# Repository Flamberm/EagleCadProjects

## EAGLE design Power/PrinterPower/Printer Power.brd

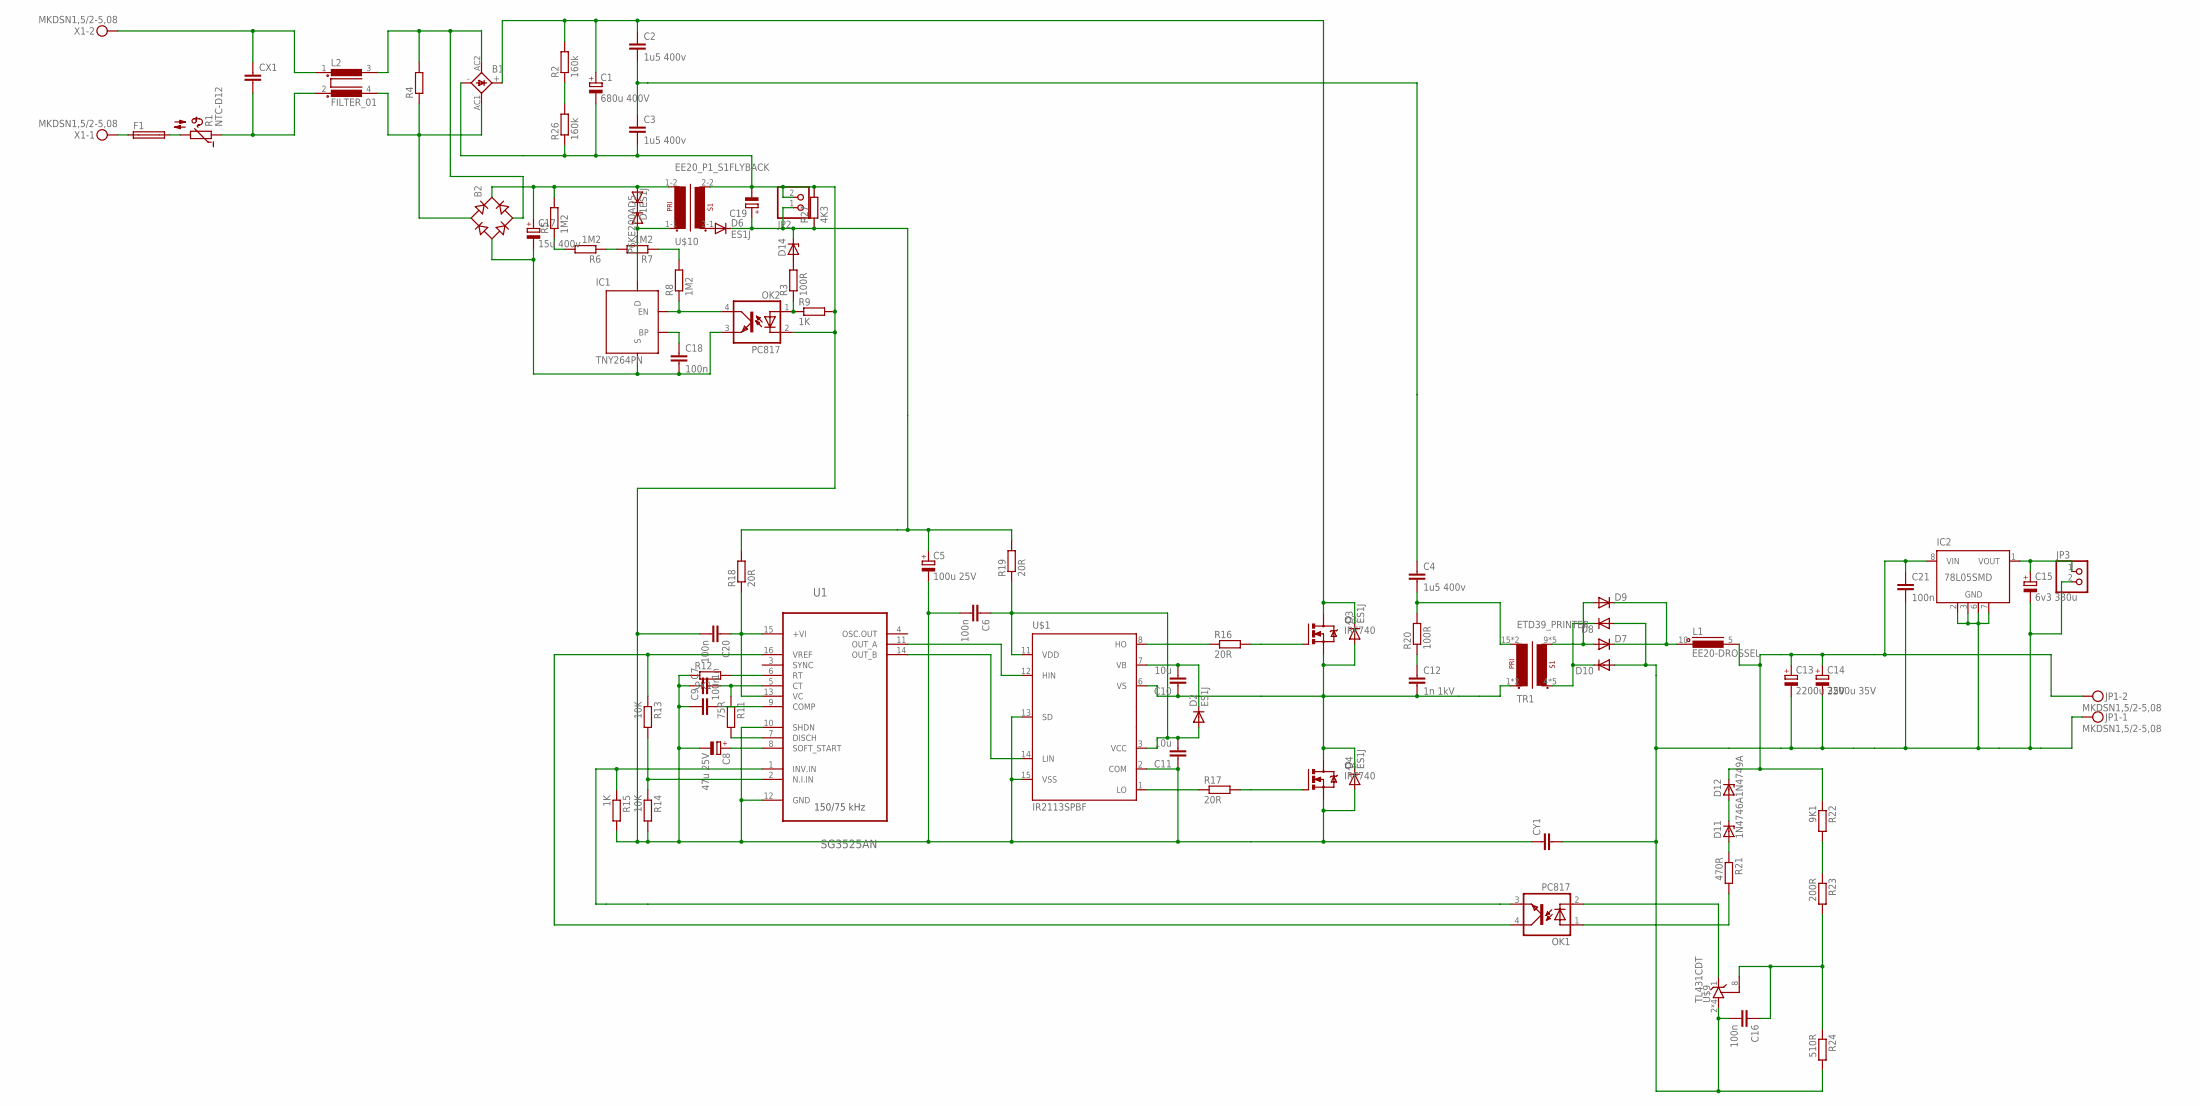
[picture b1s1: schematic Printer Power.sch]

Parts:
B1: KBL
B2: RB1A
C1: 680u 400V; EB35D
C2, C3, C4: 1u5 400v; C225-074X268
C5: 100u 25V; E2,5-7
C6, C9, C16, C18, C20, C21: 100n; C0805
C7: 1n; C0805
C8: 47u 25V; E2,5-7
C10, C11: 10u; C0805
C12: 1n 1kV; C050-025X075
C13, C14: 2200u 35V; E7,5-18
C15: 6v3 330u; E2,5-7
C17: 15u 400v; E5-13
C19: CPOL-EUE2.5-7; E2,5-7
CX1: CXXC15B8; XC15B8
CY1: CYYC10B4; YC10B4
D1: P6KE200A; DO204-10
D2, D3, D4, D5, D6: ES1J; DO214AC
D7, D8, D9, D10: DIODE-DO220S; DO220S
D11: 1N4746A; DO41Z10
D12: 1N4749A; DO41Z10
D14: ZENER-DIODEDO41Z10; DO41Z10
F1: SH22,5
IC1: TNY264PN; DIP-8B
IC2: 78L05SMD; SO08
JP1: MKDSN1,5/2-5,08
JP2, JP3: PINHD-1X2; 1X02
L1: EE20-DROSSEL; EE20_DROSSEL
L2: FILTER_01; 82721K
OK1, OK2: PC817; DIL04
Q3, Q4: IRF740; TO220BV
R1: NTC-D12
R2, R26: 160k; 0207/10
R3: 100R; R0805
R4: R-EU_0309/10; 0309/10
R5, R6, R7, R8: 1M2; R0805
R9, R15: 1K; R0805
R11: 75R; R0805
R12, R22: 9K1; R0805
R13, R14: 10K; R0805
R16, R17: 20R; 0309/12
R18, R19: 20R; R2512
R20: 100R; 0617/17
R21: 470R; R0805
R23: 200R; R0805
R24: 510R; R0805
R27: 4K3; R0805
TR1: ETD39_PRINTER; ETD39_16PIN
U1: SG3525AN; DIP254P762X510-16
U$1: IR2113SPBF; SO16W
U$9: TL431CDT; SO8
U$10: EE20_P1_S1FLYBACK; EE20_P1_S1-REV-4PIN
X1: MKDSN1,5/2-5,08

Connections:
HV-0: B1.-, C1.-, C3.2, C5.-, C6.2, C7.1, C8.-, C9.1, C11.1, C19.-, C20.2, CY1.1, D4.A, JP2.2, OK2.2 (C), Q4.S, R9.2, R12.1, R14.2, R15.2, R26.1, R27.2, U1.10 (SHDN), U1.12 (GND), U$1.2 (COM), U$1.13 (SD), U$1.15 (VSS), U$10.2-2 (S1-2)
HV-150: C2.2, C3.1, C4.1
HV-300: B1.+, C1.+, C2.1, D3.C, Q3.D, R2.2
unnamed: F1.1, X1.1
unnamed: F1.2, R1.2
unnamed: CX1.2, L2.2 (3), R1.1
unnamed: D7.C, D9.C, L1.10 (1)
unnamed: R16.1, U$1.8 (HO)
unnamed: R17.1, U$1.1 (LO)
unnamed: Q3.G, R16.2
unnamed: OK1.3 (EMIT), R15.1, U1.1 (INV.IN)
unnamed: C4.2, R20.2, TR1.15 (P1-2), TR1.16 (P1-2)
unnamed: C20.1, R18.1, U1.13 (VC), U1.15 (+VI)
unnamed: B1.AC1 (AC2), B2.AC1, L2.4, R4.1
unnamed: CX1.1, L2.1, X1.2
unnamed: B2.-, C17.-, C18.2, IC1.2 (S), IC1.3 (S), IC1.7 (S), IC1.8 (S), OK2.3 (EMIT)
unnamed: B1.AC2 (AC1), B2.AC2, L2.3 (2), R4.2
unnamed: C7.2, R11.1, U1.5 (CT)
unnamed: R11.2, U1.7 (DISCH)
unnamed: Q4.G, R17.2
unnamed: U1.11 (OUT_A), U$1.12 (HIN)
unnamed: U1.14 (OUT_B), U$1.14 (LIN)
unnamed: R12.2, U1.6 (RT)
unnamed: C8.+, U1.8 (SOFT_START)
unnamed: C9.2, U1.9 (COMP)
unnamed: OK1.4 (COL), R13.1, U1.16 (VREF)
unnamed: R13.2, R14.1, U1.2 (N.I.IN)
unnamed: IC1.4 (EN), OK2.4 (COL), R8.1
unnamed: C13.-, C14.-, C15.-, C16.2, C21.2, CY1.2, D8.A, D10.A, IC2.2 (GND), IC2.3 (GND), IC2.6 (GND), IC2.7 (GND), JP1.1, JP3.2, R24.2, U$9.2 (A), U$9.3 (A), U$9.6 (A), U$9.7 (A)
unnamed: D8.C, D10.C, TR1.4 (S1-1), TR1.5 (S1-1), TR1.6 (S1-1), TR1.7 (S1-1), TR1.8 (S1-1)
unnamed: R5.1, R6.2
unnamed: R6.1, R7.2
unnamed: C12.1, R20.1
unnamed: D7.A, D9.A, TR1.9 (S1-2), TR1.10 (S1-2), TR1.11 (S1-2), TR1.12 (S1-2), TR1.13 (S1-2)
unnamed: C15.+, IC2.1 (VOUT), JP3.1
unnamed: C13.+, C14.+, C21.1, D12.C, IC2.8 (VIN), JP1.2, L1.5 (2), R22.1
unnamed: D11.C, D12.A
unnamed: D11.A, R21.1
unnamed: OK1.1 (A), R21.2
unnamed: OK1.2 (C), U$9.1 (C)
unnamed: C16.1, R23.2, R24.1, U$9.8 (R)
unnamed: R22.2, R23.1
unnamed: R2.1, R26.2
unnamed: C5.+, C19.+, D6.C, D14.C, JP2.1, R18.2, R19.2, R27.1
unnamed: R7.1, R8.2
unnamed: D1.C, D5.C
unnamed: D5.A, IC1.5 (D), U$10.1-1
unnamed: D14.A, R3.2
unnamed: C18.1, IC1.1 (BP)
unnamed: B2.+, C17.+, D1.A, R5.2, U$10.1-2
unnamed: D6.A, U$10.2-1 (S1-1)
unnamed: OK2.1 (A), R3.1, R9.1
VB: C10.2, D2.C, U$1.7 (VB)
VCC: C6.1, C11.2, D2.A, R19.1, U$1.3 (VCC), U$1.11 (VDD)
VS: C10.1, C12.2, D3.A, D4.C, Q3.S, Q4.D, TR1.1 (P1-1), TR1.2 (P1-1), U$1.6 (VS)

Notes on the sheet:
150/75 kHz

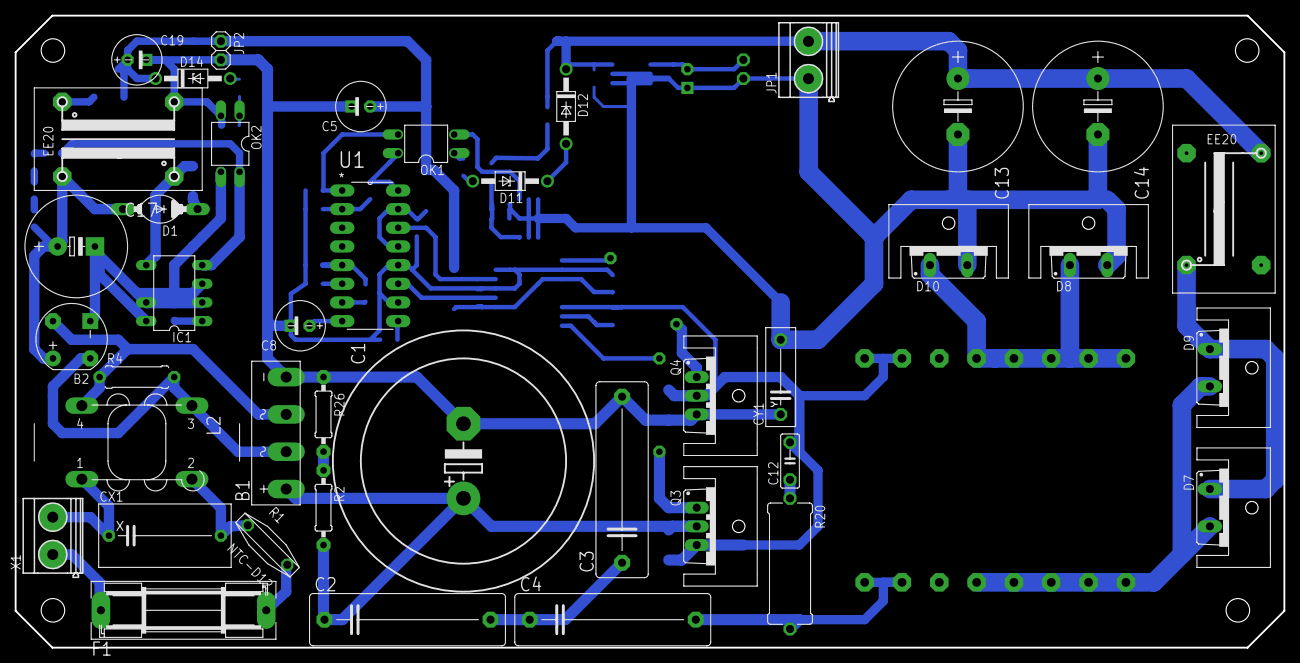
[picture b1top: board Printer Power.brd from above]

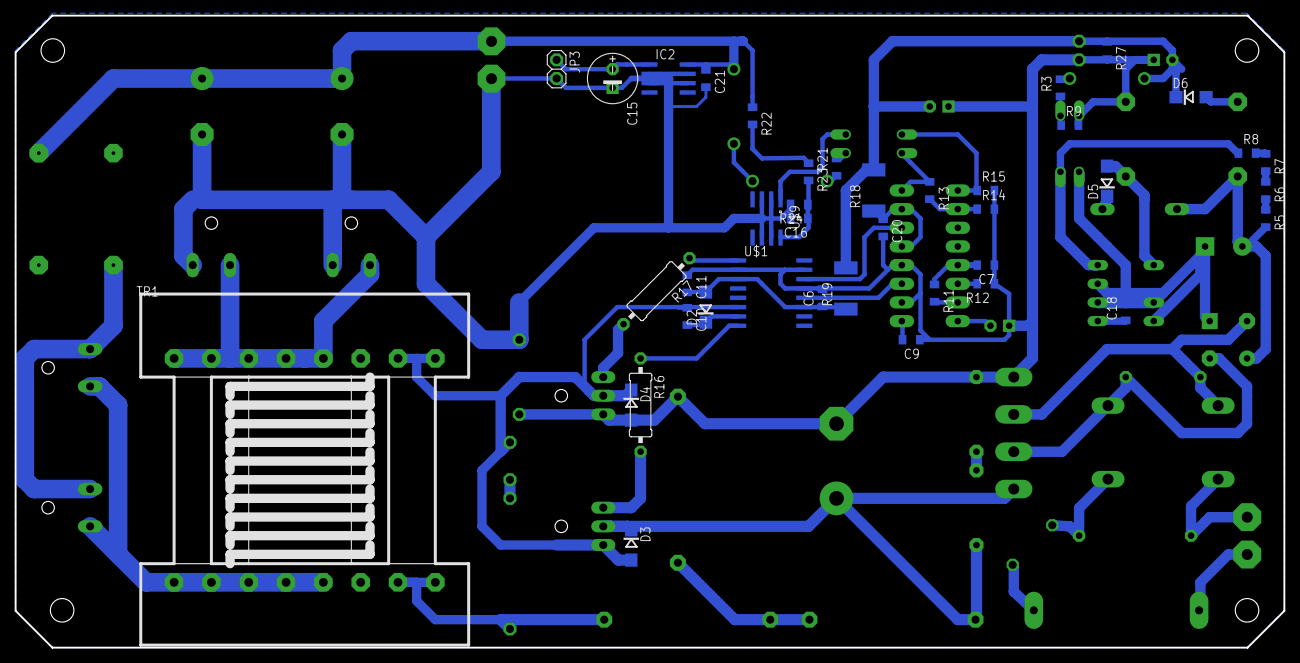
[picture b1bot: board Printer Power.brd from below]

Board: 2 copper layers, 172.7 x 86.0 mm, 87 parts (40 on the bottom side), 55 nets.

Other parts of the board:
U$3, U$4, U$5, U$6, U$7, U$8: SK95-3M3_HOLE

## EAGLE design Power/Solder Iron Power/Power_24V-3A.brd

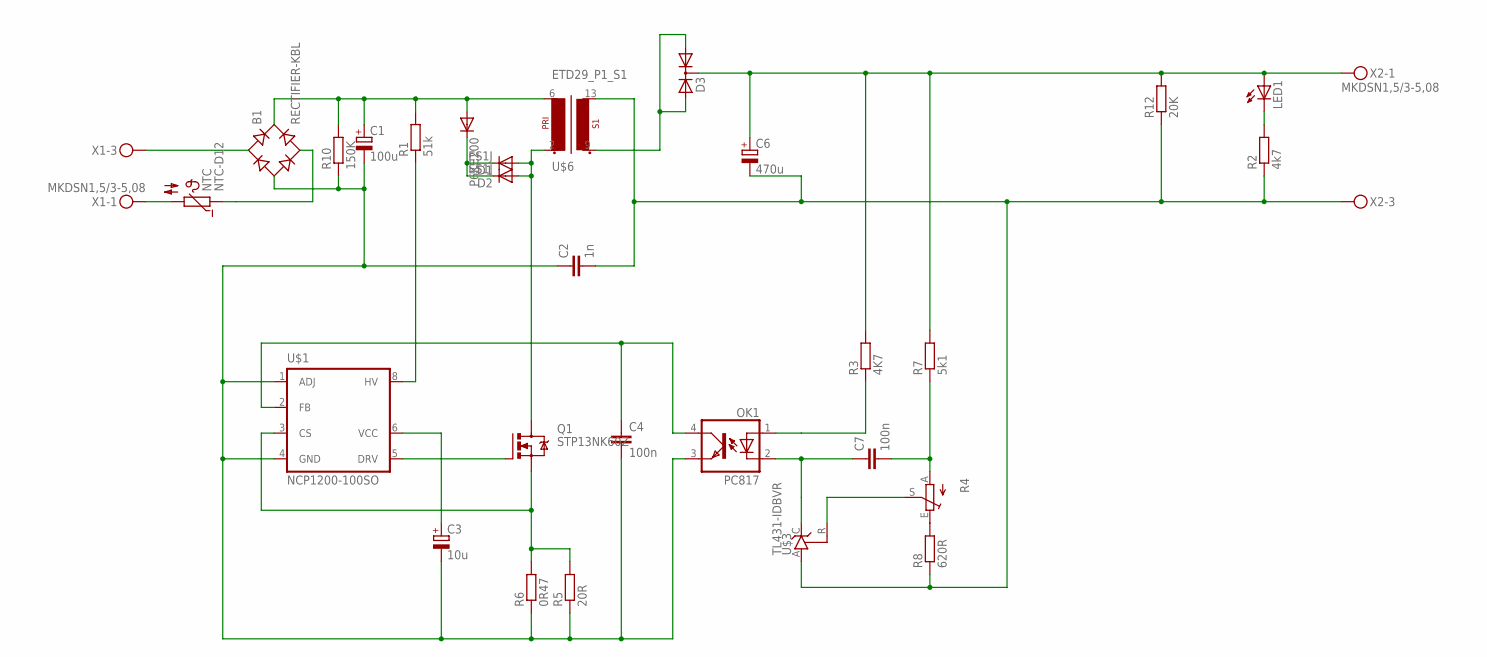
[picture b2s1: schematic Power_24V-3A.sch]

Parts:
B1: RECTIFIER-KBL; KBL
C1: 100u; EB22,5D
C2: 1n; C050-024X044
C3: 10u; E5-5
C4, C7: 100n; C0805
C6: 470u; E5-10,5
D1, D2: ES1J; DO41-7.6
D3: DIODE-2AC|CATO220V; TO220ABS
LED1: LED5MM
NTC: NTC-D12
OK1: PC817; DIL04
P6KE200: DIODE-DO15-12; DO15-12
Q1: STP13NK60Z; TO220BV
R1: 51k; SQP-5
R2: 4k7; R1206
R3: 4K7; R1206
R4: TRIM_EU-S75H; S75H
R5: 20R; 0411/12
R6: 0R47; 0411/12
R7: 5k1; R1206
R8: 620R; R1206
R10: 150K; 0207/10
R12: 20K; R1206
U$1: NCP1200-100SO; SOP8
U$3: TL431-IDBVR; SOT23-5
U$6: ETD29_P1_S1; ETD29
X1, X2: MKDSN1,5/3-5,08

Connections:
unnamed: NTC.2, X1.1
unnamed: B1.AC1, X1.3
unnamed: B1.AC2, NTC.1
unnamed: Q1.S, R5.2, R6.2, U$1.3 (CS)
unnamed: B1.-, C1.-, C2.1, C3.-, C4.2, OK1.3 (EMIT), R5.1, R6.1, R10.1, U$1.1 (ADJ), U$1.4 (GND)
unnamed: B1.+, C1.+, P6KE200.A, R1.2, R10.2, U$6.6 (P1-2)
unnamed: D1.C, D2.C, P6KE200.C
unnamed: D1.A, D2.A, Q1.D, U$6.2 (P1-1)
unnamed: C2.2, C6.-, R2.1, R8.1, R12.1, U$3.A, U$6.13 (S1-2), X2.3
unnamed: R1.1, U$1.8 (HV)
unnamed: Q1.G, U$1.5 (DRV)
unnamed: D3.A1, D3.A2, U$6.9 (S1-1)
unnamed: LED1.K (C), R2.2
unnamed: C3.+, U$1.6 (VCC)
unnamed: C4.1, OK1.4 (COL), U$1.2 (FB)
unnamed: C6.+, D3.C, LED1.A, R3.2, R7.2, R12.2, X2.1
unnamed: R4.S, U$3.R
unnamed: OK1.1 (A), R3.1
unnamed: C7.1, OK1.2 (C), U$3.C
unnamed: C7.2, R4.A, R7.1
unnamed: R4.E, R8.2

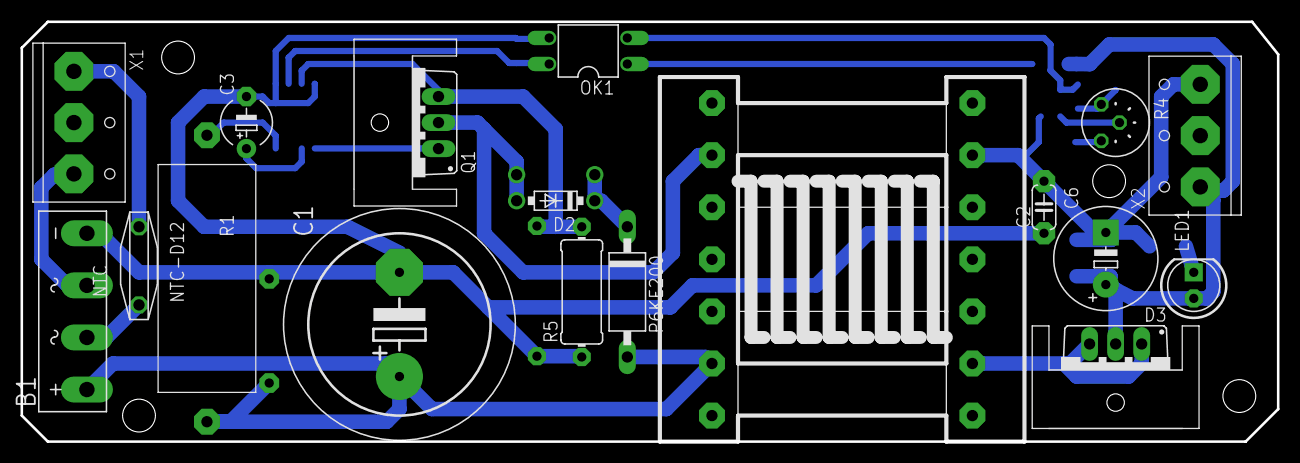
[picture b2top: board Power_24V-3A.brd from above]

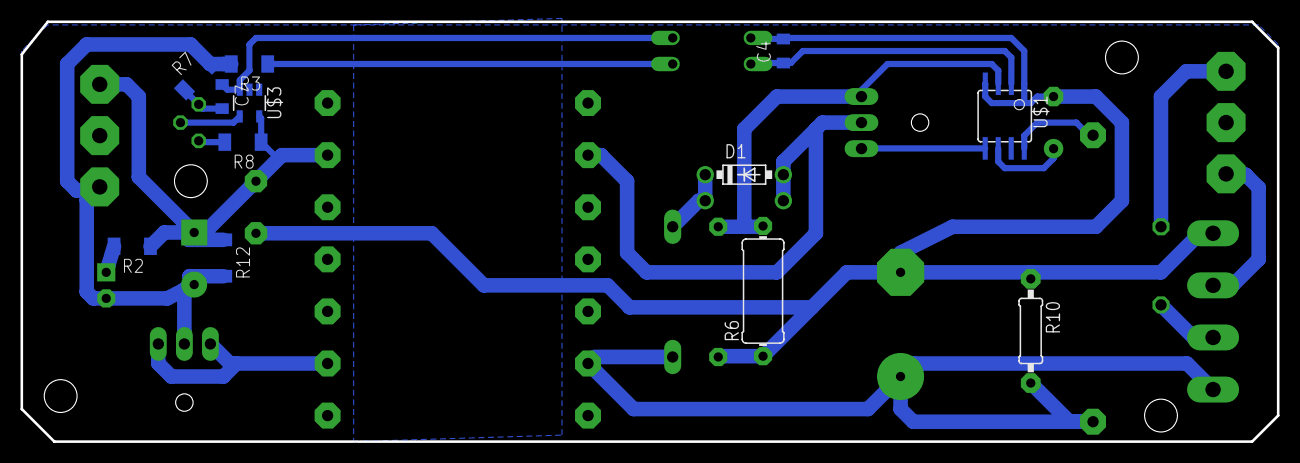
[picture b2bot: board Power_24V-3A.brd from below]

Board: 2 copper layers, 122.5 x 40.9 mm, 32 parts (12 on the bottom side), 21 nets.

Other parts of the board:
U$4, U$5: SK95-3M3_HOLE

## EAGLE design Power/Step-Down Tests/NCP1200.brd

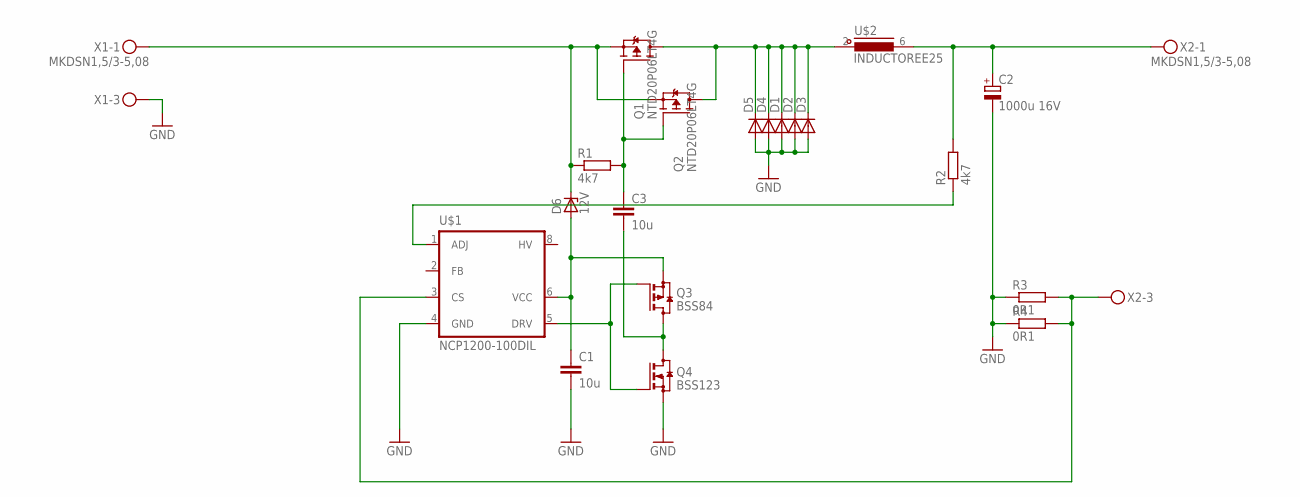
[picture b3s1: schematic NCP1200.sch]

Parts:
C1, C3: 10u; C1210
C2: 1000u 16V; E3,5-8
D1, D2, D3, D4, D5: DIODE-DO-214AC; DO-214AC
D6: 12V; SOD80C
Q1, Q2: NTD20P06LT4G; TO252
Q3: BSS84; SOT23
Q4: BSS123; SOT23
R1, R2: 4k7; R0805
R3, R4: 0R1; SQP-10
U$1: NCP1200-100DIL; DIP08
U$2: INDUCTOREE25; EE25_8PIN_HORIZ
X1, X2: MKDSN1,5/3-5,08

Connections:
GND: C1.2, C2.-, D1.A, D2.A, D3.A, D4.A, D5.A, Q4.2 (S), R3.P$1 (1), R4.P$1 (1), U$1.4 (GND), X1.3
unnamed: D6.C, Q1.2 (S), Q2.2 (S), R1.1, X1.1
unnamed: C1.1, D6.A, Q3.2 (S), U$1.6 (VCC)
unnamed: D1.C, D2.C, D3.C, D4.C, D5.C, Q1.3 (D), Q2.3 (D), U$2.2 (1)
unnamed: C3.1, Q1.1 (G), Q2.1 (G), R1.2
unnamed: R2.1, U$1.1 (ADJ)
unnamed: Q3.1 (G), Q4.1 (G), U$1.5 (DRV)
unnamed: R3.P$2 (2), R4.P$2 (2), U$1.3 (CS), X2.3
unnamed: C2.+, R2.2, U$2.6 (2), X2.1
unnamed: C3.2, Q3.3 (D), Q4.3 (D)

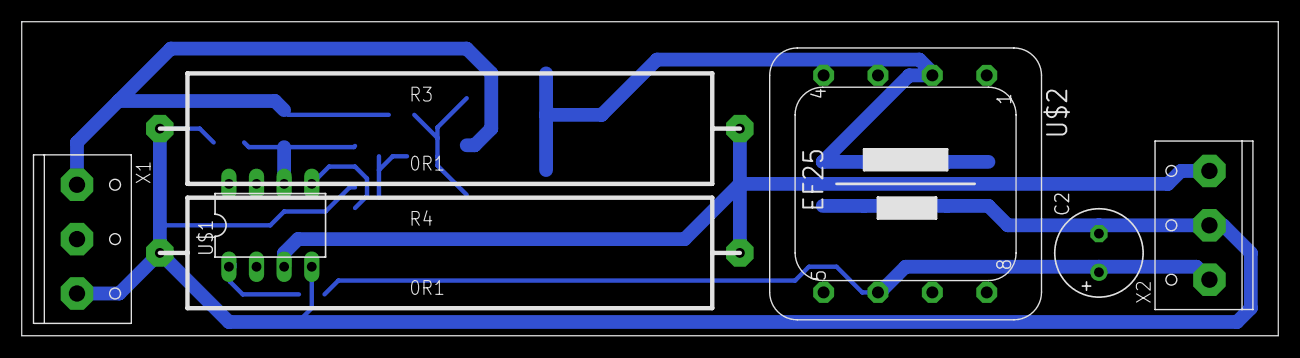
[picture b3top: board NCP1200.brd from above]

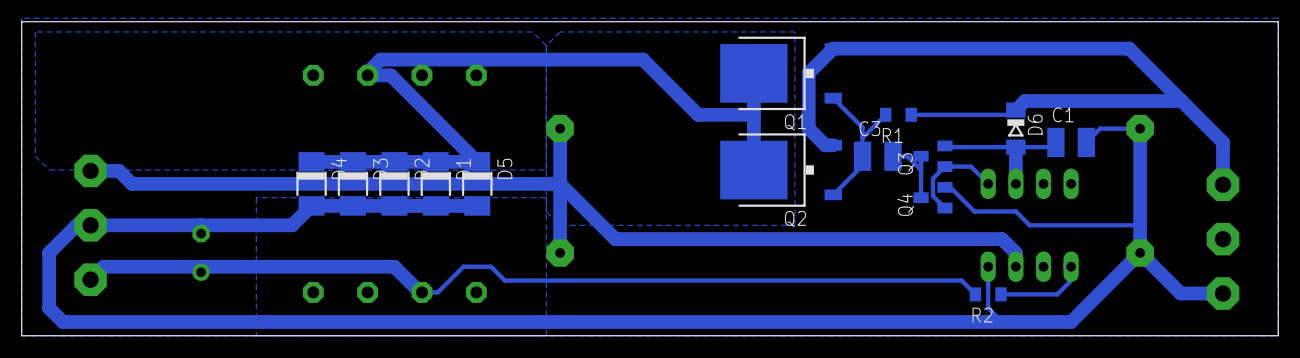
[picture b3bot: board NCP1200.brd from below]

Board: 2 copper layers, 115.5 x 28.9 mm, 21 parts (14 on the bottom side), 10 nets.

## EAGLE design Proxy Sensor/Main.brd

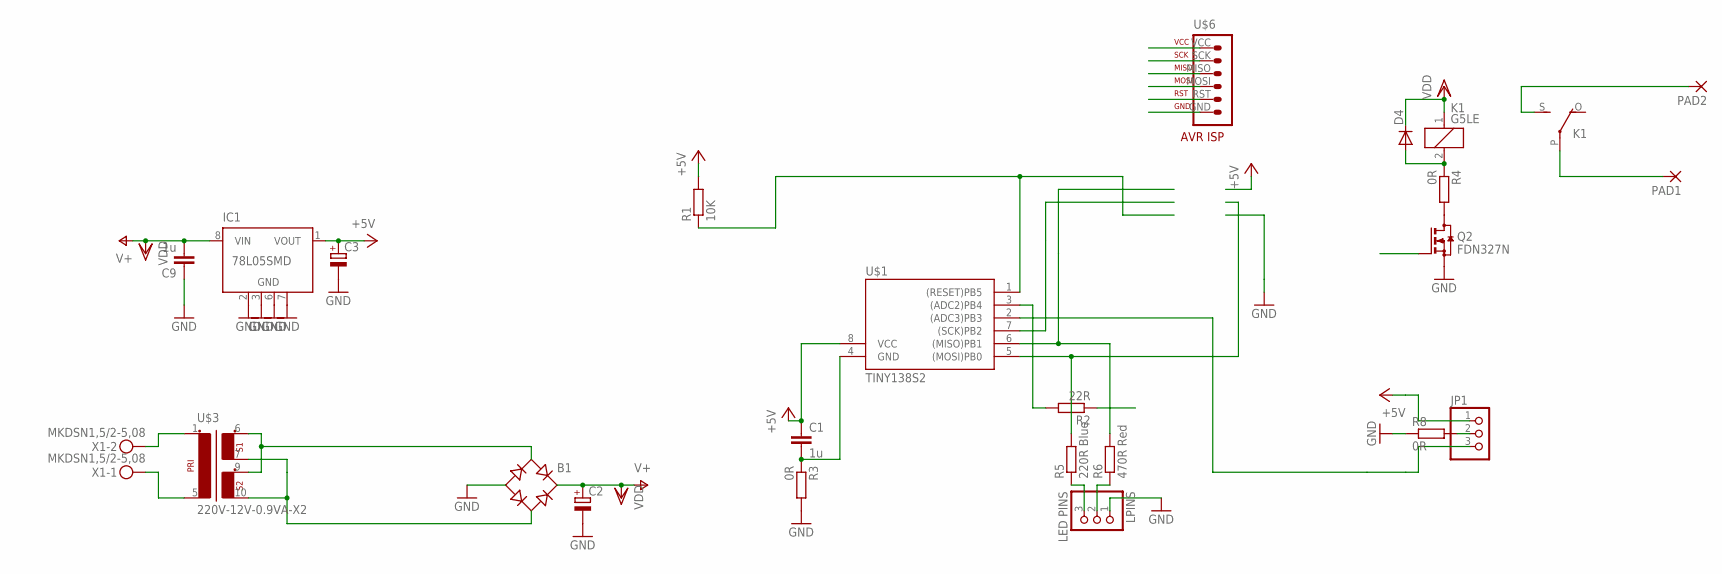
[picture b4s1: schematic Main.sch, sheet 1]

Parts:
B1: RB1A
C1, C9: 1u; C1206
C2: CPOL-EUE5-13; E5-13
C3: CPOL-EUE2.5-7; E2,5-7
D4: DIODE-DO-214AC; DO-214AC
IC1: 78L05SMD; SO08
JP1: PINHD-1X3/90; 1X03/90
K1: G5LE
LPINS: LED PINS; 1X03
PAD1, PAD2: 3,81/1,4
Q2: FDN327N; SOT23
R1: 10K; R1206
R2: 22R; R1206
R3, R4, R8: 0R; R1206
R5: 220R Blue; R1206
R6: 470R Red; R1206
U$1: TINY138S2; SO08
U$3: 220V-12V-0.9VA-X2; 32.5-27.5-22
U$6: AVR-ISP-6-ROW
X1: MKDSN1,5/2-5,08

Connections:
+5V: C1.1, C3.+, IC1.1 (VOUT), JP1.1, R1.2, U$1.8 (VCC), U$6.VCC
GND: B1.-, C2.-, C3.-, C9.1, IC1.2 (GND), IC1.3 (GND), IC1.6 (GND), IC1.7 (GND), LPINS.1, Q2.2 (S), R3.2, R8.1, U$6.GND
unnamed: R1.1, U$1.1 ((RESET)PB5), U$6.RST
unnamed: U$1.7 ((SCK)PB2), U$6.SCK
unnamed: R6.2, U$1.6 ((MISO)PB1), U$6.MISO
unnamed: R5.2, U$1.5 ((MOSI)PB0), U$6.MOSI
unnamed: Q2.1 (G), R2.1
unnamed: R2.2, U$1.3 ((ADC2)PB4)
unnamed: LPINS.3, R5.1
unnamed: LPINS.2, R6.1
unnamed: D4.A, K1.2, R4.1
unnamed: U$3.1 (P1-1), X1.2
unnamed: U$3.5 (P1-2), X1.1
unnamed: B1.AC1, U$3.6 (S1-1), U$3.9 (S2-1)
unnamed: B1.AC2, U$3.7 (S1-2), U$3.10 (S2-2)
unnamed: Q2.3 (D), R4.2
unnamed: C1.2, R3.1, U$1.4 (GND)
unnamed: K1.P, PAD1.1
unnamed: K1.S, PAD2.1
unnamed: JP1.2, R8.2
unnamed: JP1.3, U$1.2 ((ADC3)PB3)
VDD: B1.+, C2.+, C9.2, D4.C, IC1.8 (VIN), K1.1

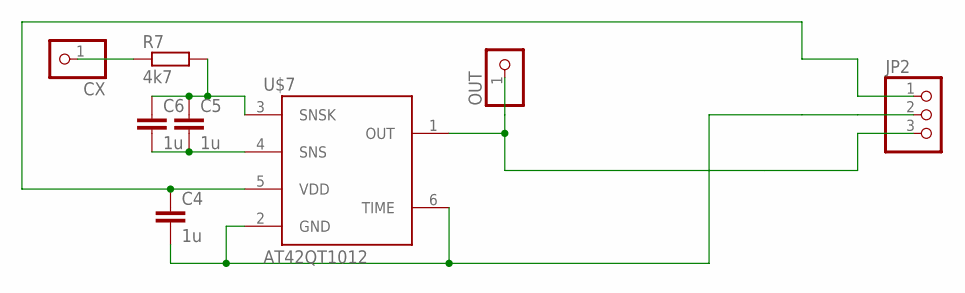
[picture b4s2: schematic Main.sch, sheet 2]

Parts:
C4, C5, C6: 1u; C1206
CX: PINHD-1X1; 1X01
JP2: PINHD-1X3/90; 1X03/90
OUT: PINHD-1X1; 1X01
R7: 4k7; R1206
U$7: AT42QT1012; SOT23-6

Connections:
unnamed: CX.1, R7.1
unnamed: C5.2, C6.2, U$7.4 (SNS)
unnamed: JP2.3, OUT.1, U$7.1 (OUT)
unnamed: C5.1, C6.1, R7.2, U$7.3 (SNSK)
unnamed: C4.1, JP2.1, U$7.5 (VDD)
unnamed: C4.2, JP2.2, U$7.2 (GND), U$7.6 (TIME)

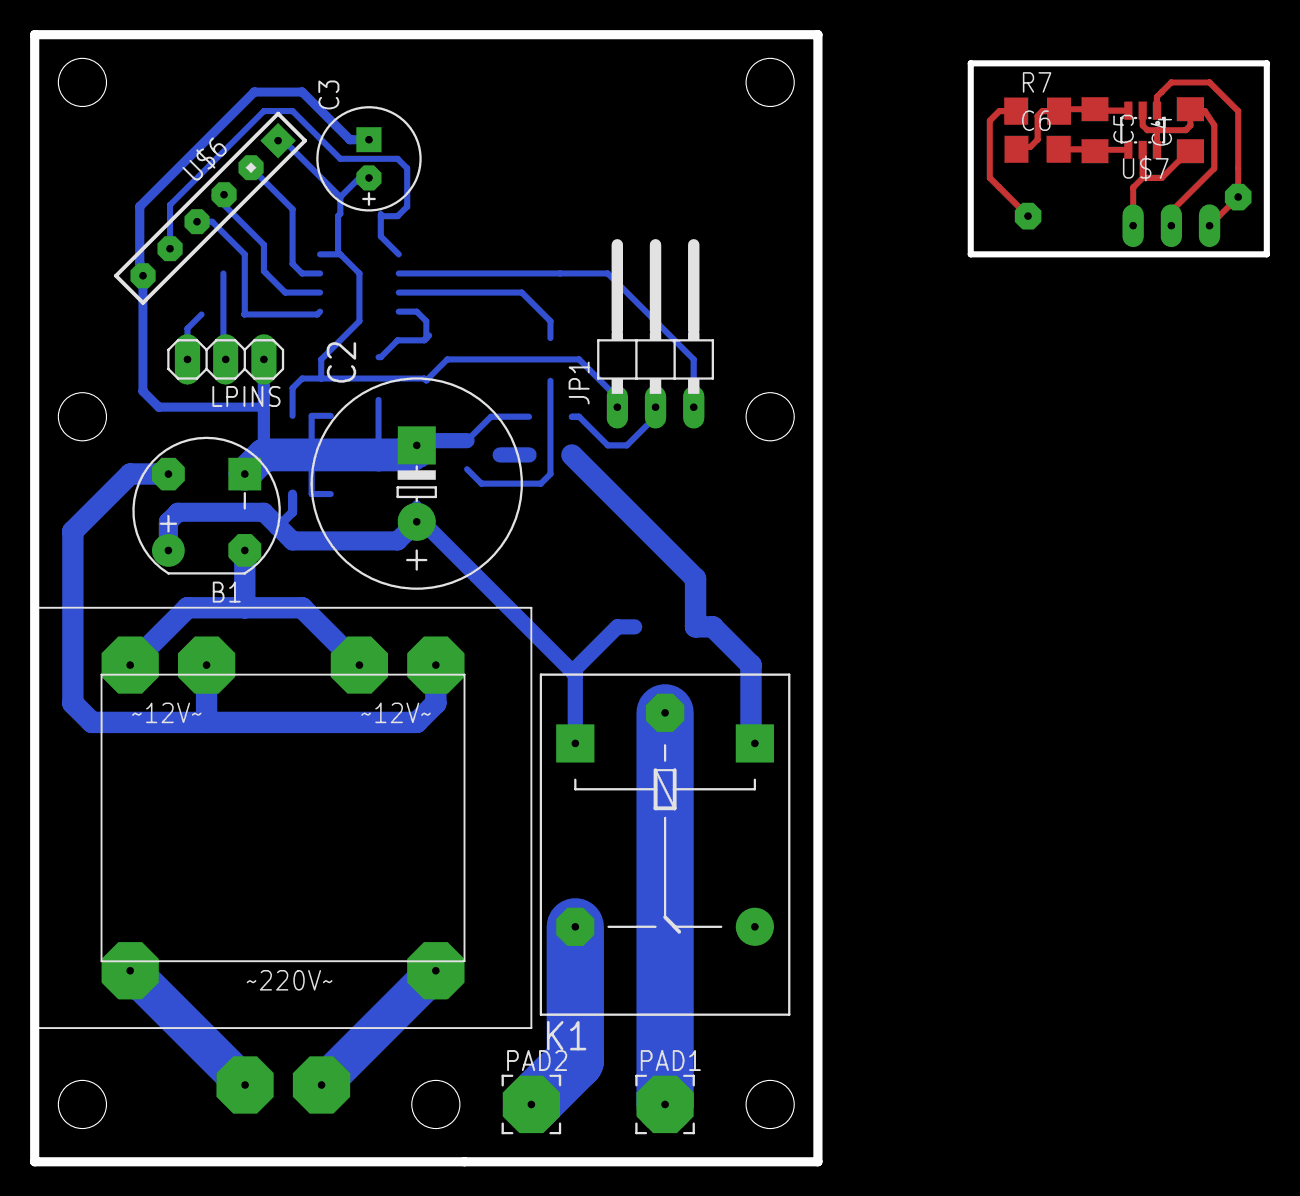
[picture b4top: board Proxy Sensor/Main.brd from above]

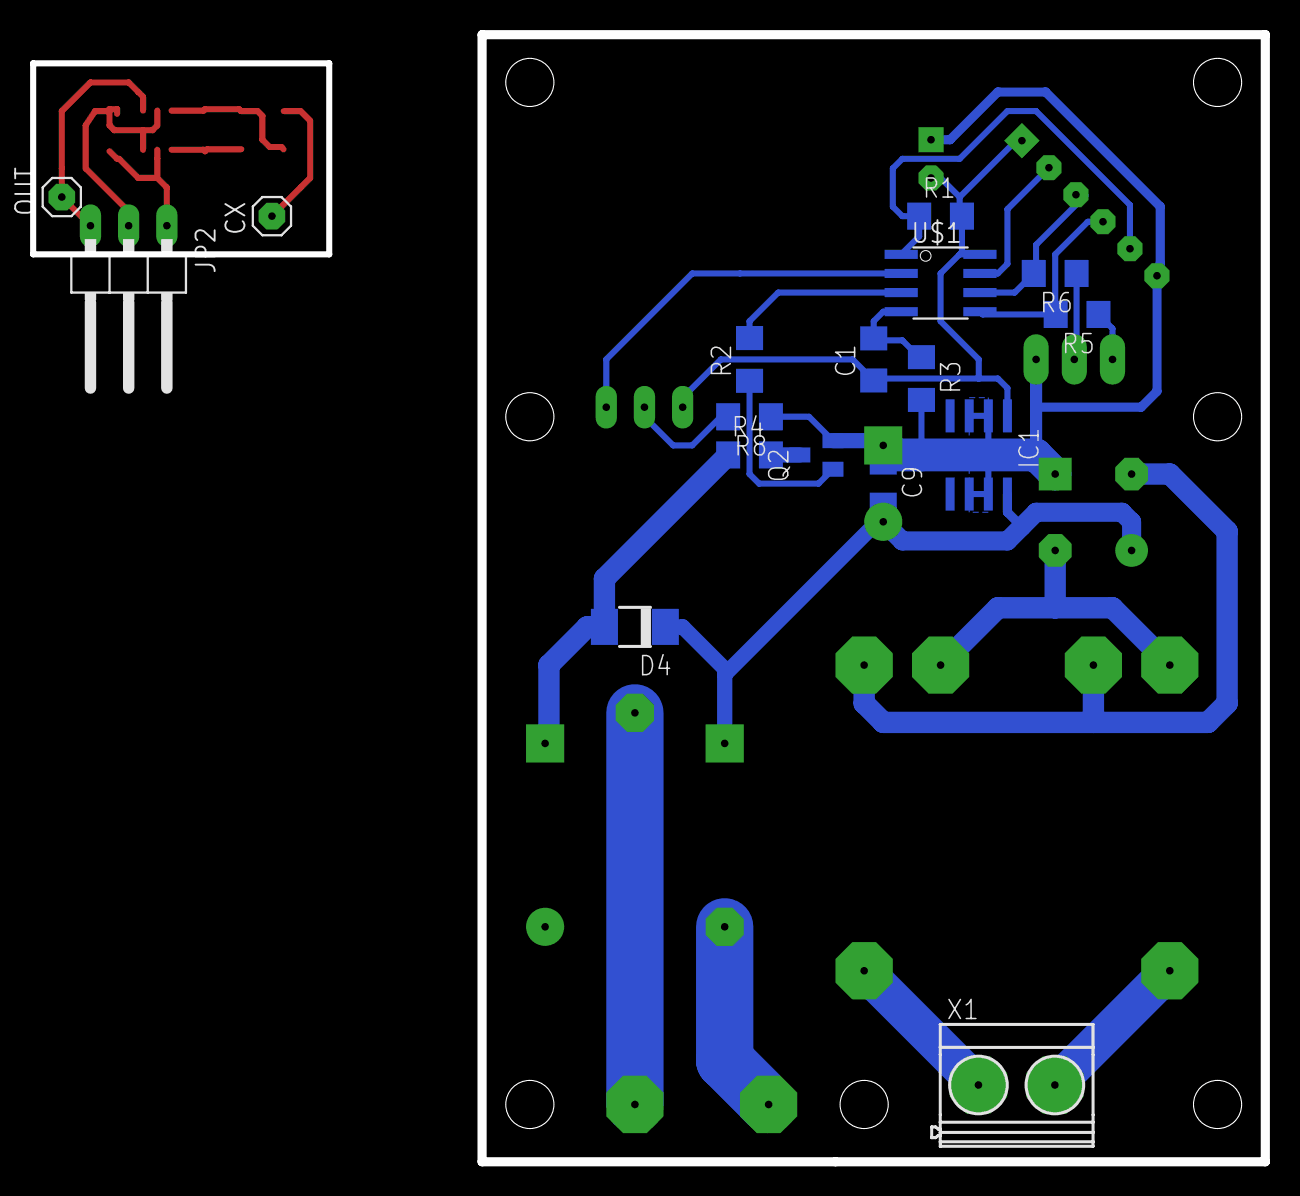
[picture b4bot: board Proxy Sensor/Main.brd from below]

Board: 2 copper layers, 81.9 x 74.9 mm, 32 parts (17 on the bottom side), 28 nets.

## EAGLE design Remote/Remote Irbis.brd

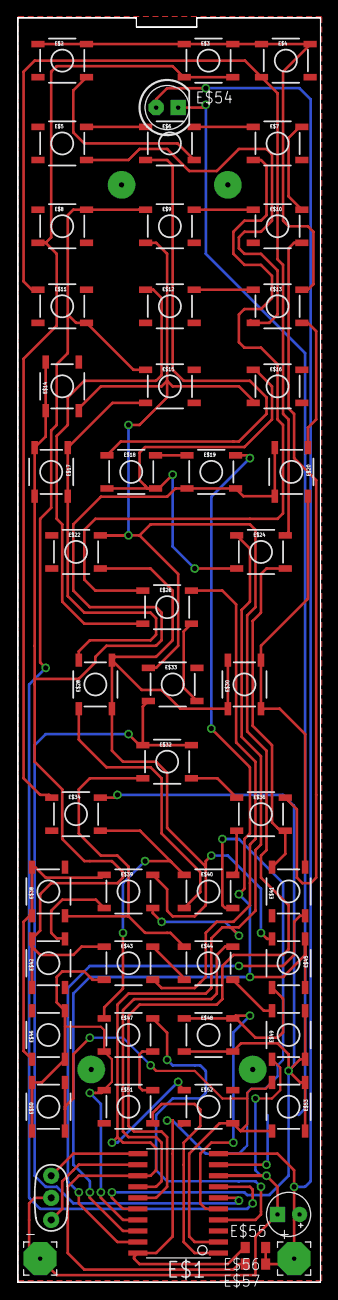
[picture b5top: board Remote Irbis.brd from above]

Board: 2 copper layers, 34.8 x 145.4 mm, 53 parts (1 on the bottom side), 21 nets.

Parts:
+: 3,81/1,4
-: 3,81/1,4
E$1: SO20L$
E$2, E$3, E$4, E$5, E$6, E$7, E$8, E$9, E$10, E$11, E$12, E$13, E$14, E$15, E$16, E$17, E$18, E$19, E$20, E$22, E$24, E$26, E$28, E$30, E$32, E$33, E$34, E$36, E$38, E$39, E$40, E$41, E$42, E$43, E$44, E$45, E$46, E$47, E$48, E$49, E$50, E$51, E$52, E$53: TACTILE-SWITCH-SMD
E$21: R1206
E$54: LED5MM
E$55: E2,5-5
E$56, E$57: 100K; R0805
E$59: RESONATOR-PTH

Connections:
S$1: E$1.6, E$2.1, E$2.2, E$3.1, E$3.2, E$4.1, E$4.2, E$12.1, E$12.2, E$13.1, E$13.2, E$26.3, E$26.4, E$32.1, E$32.2, E$33.3, E$33.4
S$2: E$12.3, E$12.4
S$3: E$1.16, E$3.3, E$3.4, E$8.3, E$8.4, E$34.1, E$34.2, E$48.3, E$48.4, E$49.3, E$49.4, E$53.1, E$53.2
S$4: E$1.13, E$4.3, E$4.4, E$11.1, E$11.2, E$24.1, E$24.2, E$39.3, E$39.4, E$42.3, E$42.4, E$52.1, E$52.2, E$57.2
S$5: +.1, E$1.10, E$54.A, E$55.+, E$56.1, E$57.1
S$6: E$1.19, E$5.3, E$5.4, E$13.3, E$13.4, E$20.1, E$20.2, E$30.3, E$30.4, E$41.3, E$41.4
S$7: E$1.18, E$2.3, E$2.4, E$6.3, E$6.4, E$18.1, E$18.2, E$19.1, E$19.2, E$45.1, E$45.2
S$8: E$1.17, E$7.3, E$7.4, E$26.1, E$26.2, E$43.3, E$43.4, E$46.3, E$46.4, E$47.3, E$47.4, E$50.1, E$50.2, E$51.1, E$51.2
S$9: E$1.7, E$5.1, E$5.2, E$6.1, E$6.2, E$7.1, E$7.2, E$8.1, E$8.2, E$9.1, E$9.2, E$10.1, E$10.2, E$11.3, E$11.4, E$15.1, E$15.2
S$10: E$1.15, E$9.3, E$9.4, E$14.3, E$14.4, E$16.3, E$16.4, E$22.1, E$22.2, E$33.1, E$33.2
S$11: E$21.1, E$54.K
S$12: -.1, E$1.8, E$14.1, E$14.2, E$17.3, E$17.4, E$19.3, E$19.4, E$20.3, E$20.4, E$42.1, E$42.2, E$43.1, E$43.2, E$44.3, E$44.4, E$49.1, E$49.2, E$55.-, E$59.2
S$13: E$1.14, E$10.3, E$10.4, E$32.3, E$32.4, E$36.1, E$36.2, E$38.3, E$38.4, E$44.1, E$44.2
S$14: E$1.4, E$16.1, E$16.2, E$18.3, E$18.4, E$24.3, E$24.4, E$34.3, E$34.4, E$36.3, E$36.4, E$40.1, E$40.2, E$41.1, E$41.2, E$47.1, E$47.2
S$15: E$1.20, E$15.3, E$15.4, E$17.1, E$17.2, E$28.1, E$28.2, E$40.3, E$40.4, E$56.2
S$16: E$1.11, E$59.3
S$17: E$1.12, E$59.1
S$18: E$1.5, E$22.3, E$22.4, E$28.3, E$28.4, E$30.1, E$30.2, E$38.1, E$38.2, E$39.1, E$39.2, E$45.3, E$45.4, E$46.1, E$48.1, E$48.2
S$19: E$1.9, E$21.2
S$24: E$1.2, E$50.3, E$50.4, E$52.3, E$52.4, E$53.3, E$53.4
S$25: E$1.1, E$51.3, E$51.4

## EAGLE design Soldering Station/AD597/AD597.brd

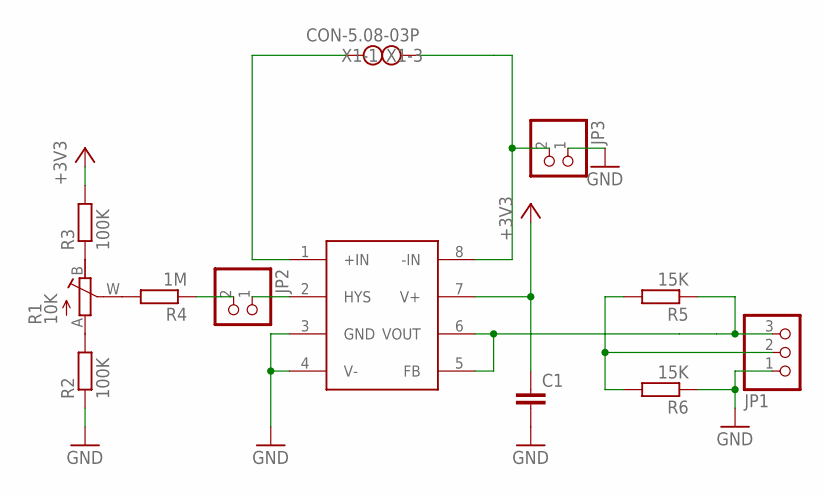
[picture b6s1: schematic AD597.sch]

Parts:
C1: CAP_0805; C0805
JP1: PINHD-1X3/90; 1X03/90
JP2, JP3: PINHD-1X2; 1X02
R1: 10K; RJ9W
R2, R3: 100K; R0805
R4: 1M; R0805
R5, R6: 15K; R0805
U$1: AD597ARZ; SO8
X1: CON-5.08-03P; MKDSN1,5/3-5,08

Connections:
+3V3: C1.1, R3.2, U$1.7 (V+)
GND: C1.2, JP1.1, JP3.1, R2.1, R6.1, U$1.3 (GND), U$1.4 (V-)
unnamed: U$1.1 (+IN), X1.3
unnamed: JP3.2, U$1.8 (-IN), X1.1
unnamed: JP1.3, R5.1, U$1.5 (FB), U$1.6 (VOUT)
unnamed: JP1.2, R5.2, R6.2
unnamed: R1.A, R2.2
unnamed: R1.B (E), R3.1
unnamed: R1.W (S), R4.2
unnamed: JP2.2, R4.1
unnamed: JP2.1, U$1.2 (HYS)

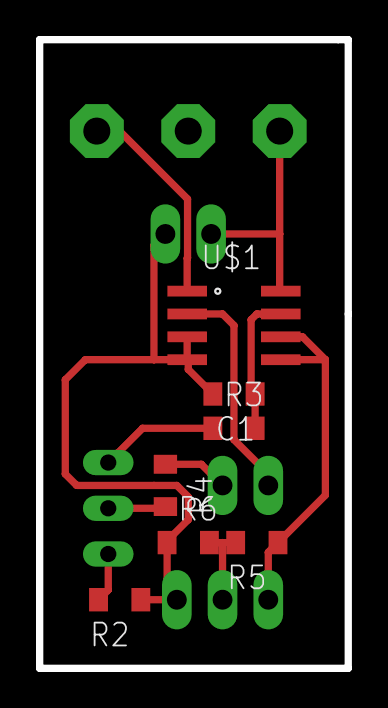
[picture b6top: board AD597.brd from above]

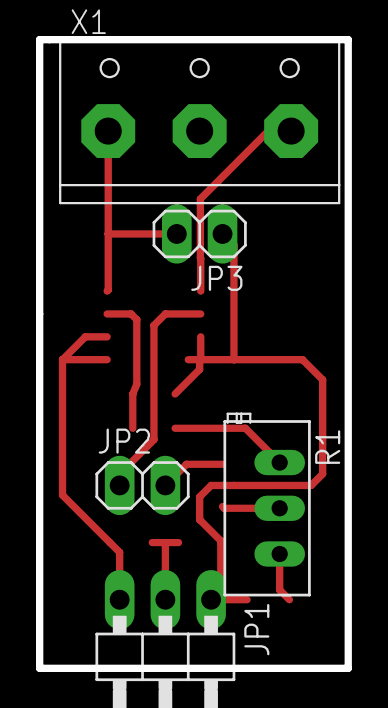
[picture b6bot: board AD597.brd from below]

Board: 2 copper layers, 17.1 x 34.9 mm, 12 parts (5 on the bottom side), 11 nets.

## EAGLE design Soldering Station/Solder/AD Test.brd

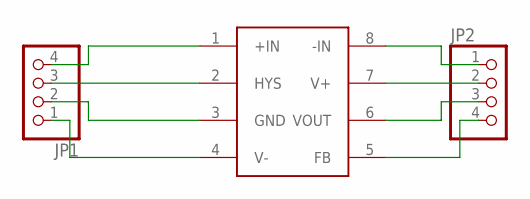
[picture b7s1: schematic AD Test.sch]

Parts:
JP1, JP2: PINHD-1X4; 1X04
U$1: AD597ARZ; SO8

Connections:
unnamed: JP1.4, U$1.1 (+IN)
unnamed: JP1.3, U$1.2 (HYS)
unnamed: JP1.2, U$1.3 (GND)
unnamed: JP1.1, U$1.4 (V-)
unnamed: JP2.1, U$1.8 (-IN)
unnamed: JP2.2, U$1.7 (V+)
unnamed: JP2.3, U$1.6 (VOUT)
unnamed: JP2.4, U$1.5 (FB)

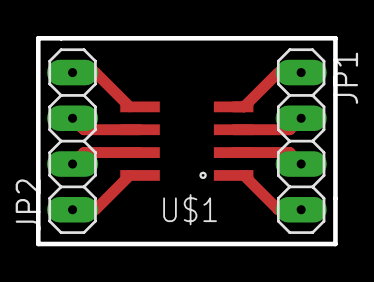
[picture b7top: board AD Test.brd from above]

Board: 2 copper layers, 16.5 x 11.4 mm, 3 parts (0 on the bottom side), 8 nets.

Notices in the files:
parts and their libraries:
SparkFun-Electromechanical: Licensing: Creative Commons ShareAlike 4.0 International - https://creativecommons.org/licenses/by-sa/4.0
